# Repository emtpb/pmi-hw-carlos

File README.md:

# PMI CApacitor Resistively LOaded and Switches (CARLOS)

This pcb is designed for the course PMI (Practical course Microcontroller and Interface electronics). It features two buttons and a simple capacitor load / discharge circuit.

Pin header and sockets are compatible with
[Digilents Pmod](https://digilent.com/reference/pmod/start) interface.

The board can be used with [PMI-BOB2](https://github.com/emtpb/pmi-hw-bob2)
pcb.

# Interactive BOM
An interactive html BOM page with pcb layout and material placement can be found [here](https://emtpb.github.io/pmi-hw-carlos/bom/ibom.html).

# Changelog

## 1.0
* First prototype

## 1.1
* First release

## 1.1.1
* Update project to Kicad 6
* Change the load resistance R1 of the capacitors from 10 kΩ to 1 kΩ

## 1.2
* Round pcb corners

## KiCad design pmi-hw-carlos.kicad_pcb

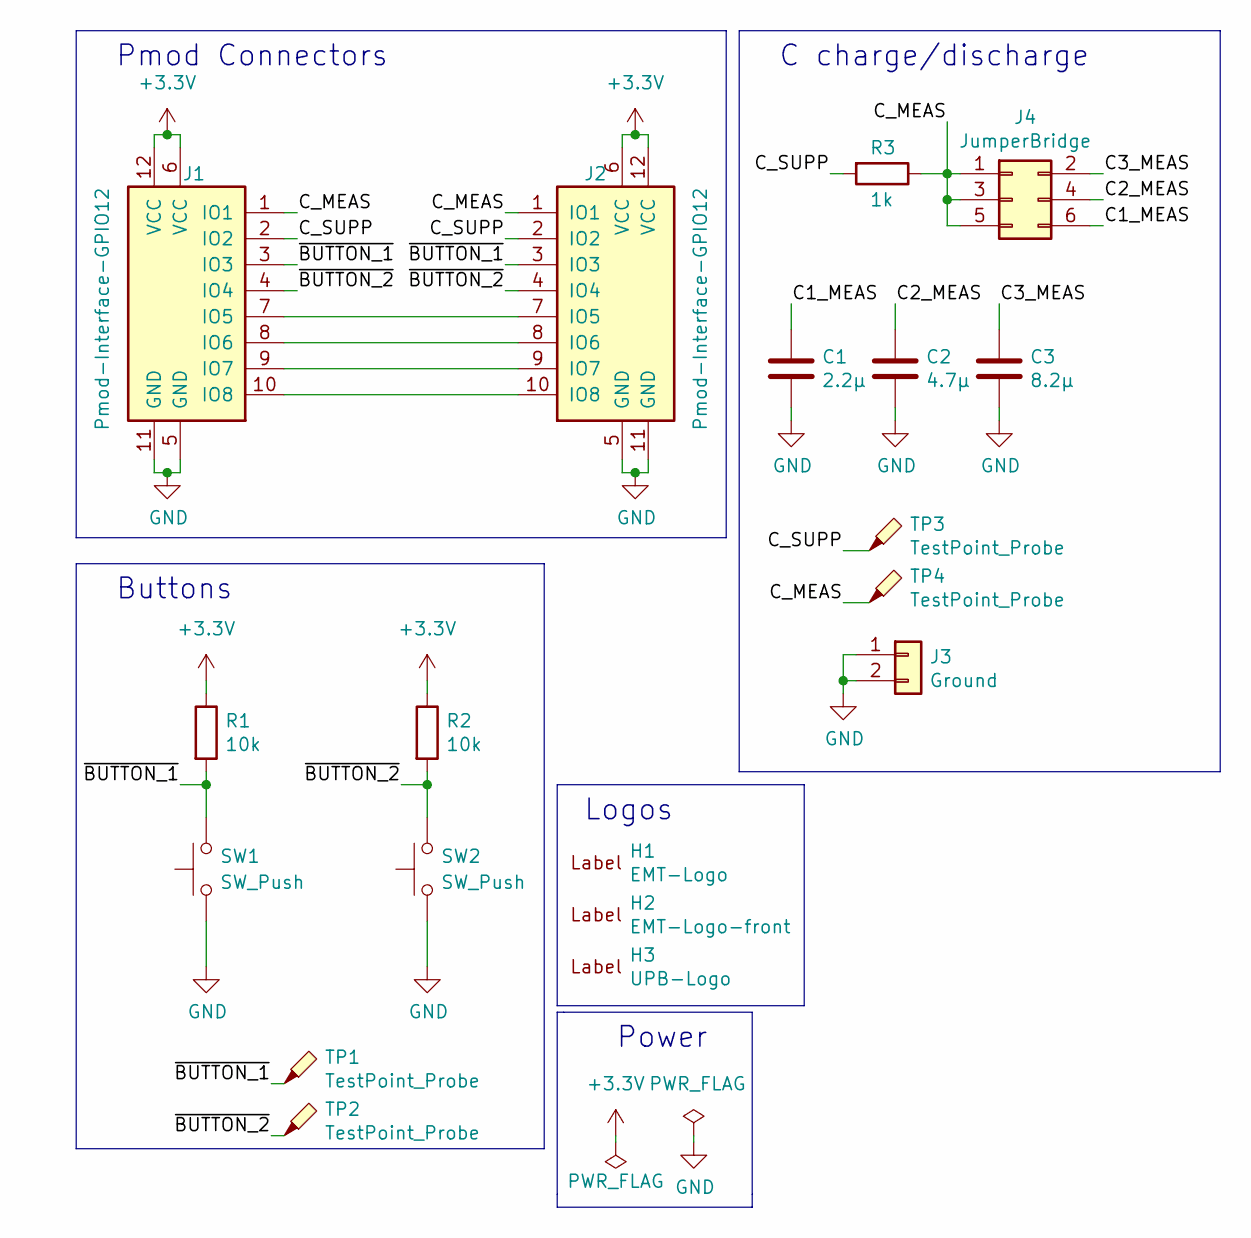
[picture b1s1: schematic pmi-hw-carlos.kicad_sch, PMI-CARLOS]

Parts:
C1: 2.2µ; C_0805_2012Metric
C2: 4.7µ; C_0805_2012Metric
C3: 8.2µ; C_0805_2012Metric
H1: EMT-Logo; EMT-Logo_8.2x4.1mm_Silkscreen
H2: EMT-Logo-front; EMT-Logo_5.1x2.5mm_Silkscreen
H3: UPB-Logo; UPB-Logo_En_12.3X4.3mm
J1: Pmod-Interface-GPIO12; Pmod_Interface_Male12
J2: Pmod-Interface-GPIO12; Pmod_Interface_Female12
J3: Ground; PinHeader_1x02_P2.54mm_Vertical
J4: JumperBridge; PinHeader_2x03_P2.54mm_Vertical
R1, R2: 10k; R_0603_1608Metric
R3: 1k; R_0603_1608Metric
SW1, SW2: SW_Push; SW_SPST_Schurter_1301.93XX
TP1, TP2, TP3, TP4: TestPoint_Probe; TestPoint_THTPad_2.5x2.5mm_Drill1.2mm

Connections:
+3.3V: J1.6 (VCC), J1.12 (VCC), J2.6 (VCC), J2.12 (VCC), R1.1, R2.1
/C1_MEAS: C1.1, J4.6
/C2_MEAS: C2.1, J4.4
/C3_MEAS: C3.1, J4.2
/C_MEAS: J1.1 (IO1), J2.1 (IO1), J4.1, J4.3, J4.5, R3.1, TP4.1
/C_SUPP: J1.2 (IO2), J2.2 (IO2), R3.2, TP3.1
/~BUTTON_1: J1.3 (IO3), J2.3 (IO3), R1.2, SW1.2, TP1.1
/~BUTTON_2: J1.4 (IO4), J2.4 (IO4), R2.2, SW2.2, TP2.1
GND: C1.2, C2.2, C3.2, J1.5 (GND), J1.11 (GND), J2.5 (GND), J2.11 (GND), J3.1, J3.2, SW1.1, SW2.1
unnamed: J1.7 (IO5), J2.7 (IO5)
unnamed: J1.8 (IO6), J2.8 (IO6)
unnamed: J1.9 (IO7), J2.9 (IO7)
unnamed: J1.10 (IO8), J2.10 (IO8)

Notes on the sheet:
Logos
Buttons
Power
C charge/discharge
Pmod Connectors

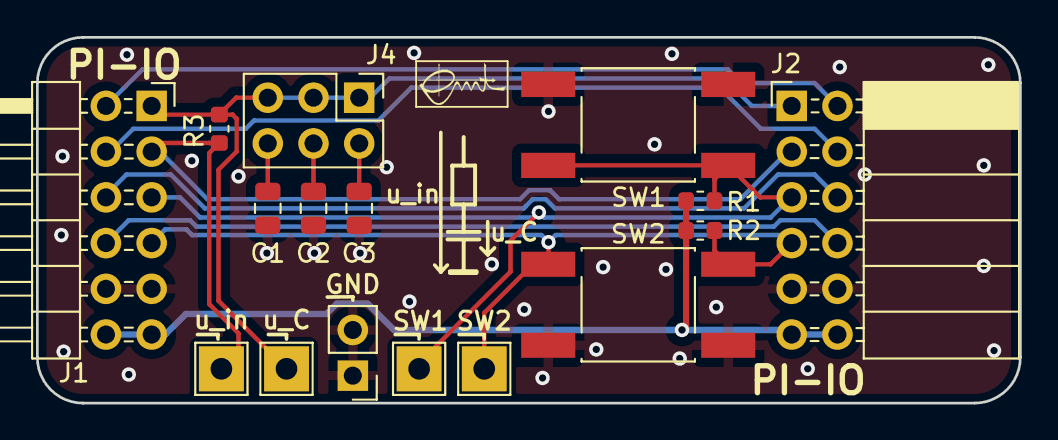
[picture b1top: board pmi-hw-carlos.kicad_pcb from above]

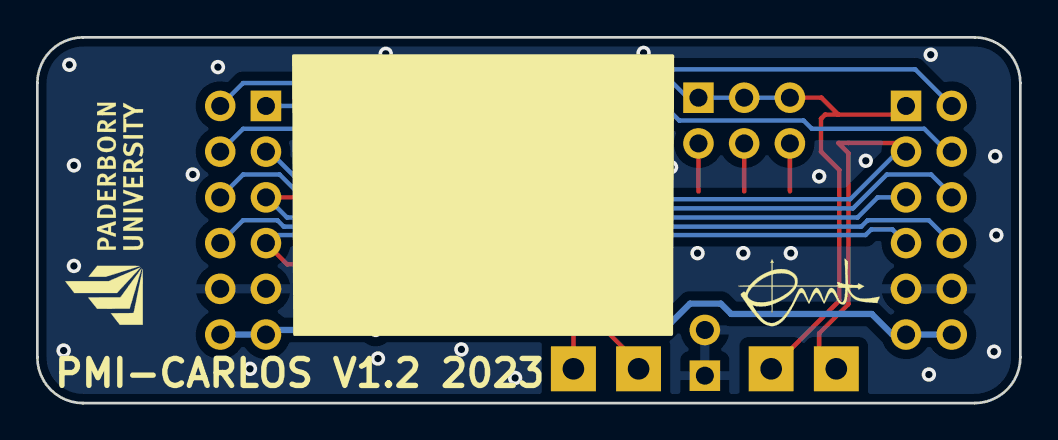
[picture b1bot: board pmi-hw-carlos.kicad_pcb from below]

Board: 2 copper layers, 54.6 x 20.3 mm, 19 parts (2 on the bottom side), 13 nets.

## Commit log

2021-12-23 Initial revision
2021-12-23 Update rescue lib
2022-09-12 Move project to Kicad 6, change load resistance R1 to 1k
2022-09-12 readme: Fix notation
2023-02-21 Bump to version 1.2
2025-05-22 Add interactive BOM link
